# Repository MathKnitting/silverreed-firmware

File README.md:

# [Silverreed Firmware](./README.md)

<!-- Table of Contents -->

- [Installation](#installation)
- [Usage](#usage)
- [License](#license)

## Installation

This project leverages:
- PlatformIO for Arduino project management
- uv for Python dependency management
- taskipy for task automation

### Prerequisites

- Python 3.12 or higher
- [uv](https://docs.astral.sh/uv/) - Fast Python package installer

### Setup

1. Clone the repo
   ```shell
   git clone https://github.com/Knitall/silverreed-firmware.git
   cd silverreed-firmware
   ```

2. Install uv (if not already installed)
   ```shell
   curl -LsSf https://astral.sh/uv/install.sh | sh
   ```

3. Install dependencies
   ```shell
   uv sync --all-groups
   ```

4. Initialize the project
   ```shell
   uv run task init
   ```

## Usage

### Common Commands

```shell
# Build the firmware
uv run task build

# Build for specific environment
uv run task build -e uno
uv run task build -e unodebug    # With debug flags
uv run task build -e uno_r4_wifi # For Arduino UNO R4

# Upload to microcontroller
uv run task upload
uv run task upload -e uno

# Run tests
uv run task test
uv run task test -e simavr       # Run on AVR simulator
uv run task test -e native       # Run on native platform

# Run linter
uv run task lint

# Open serial monitor
uv run task monitor

# Documentation
uv run task docs-serve            # Serve locally with hot-reload
uv run task docs-build            # Build static site
uv run task docs-deploy           # Deploy to GitHub Pages

# Clean build artifacts
uv run task clean

# See all available tasks
uv run task --list
```

### Available Environments

- `uno` - Arduino UNO (default)
- `unodebug` - Arduino UNO with debug flags
- `uno_r4_wifi` - Arduino UNO R4 WiFi
- `simavr` - AVR simulator for testing
- `native` - Native platform for desktop tests

## License

Distributed under the MIT License. See [LICENSE](./LICENSE) for more information.

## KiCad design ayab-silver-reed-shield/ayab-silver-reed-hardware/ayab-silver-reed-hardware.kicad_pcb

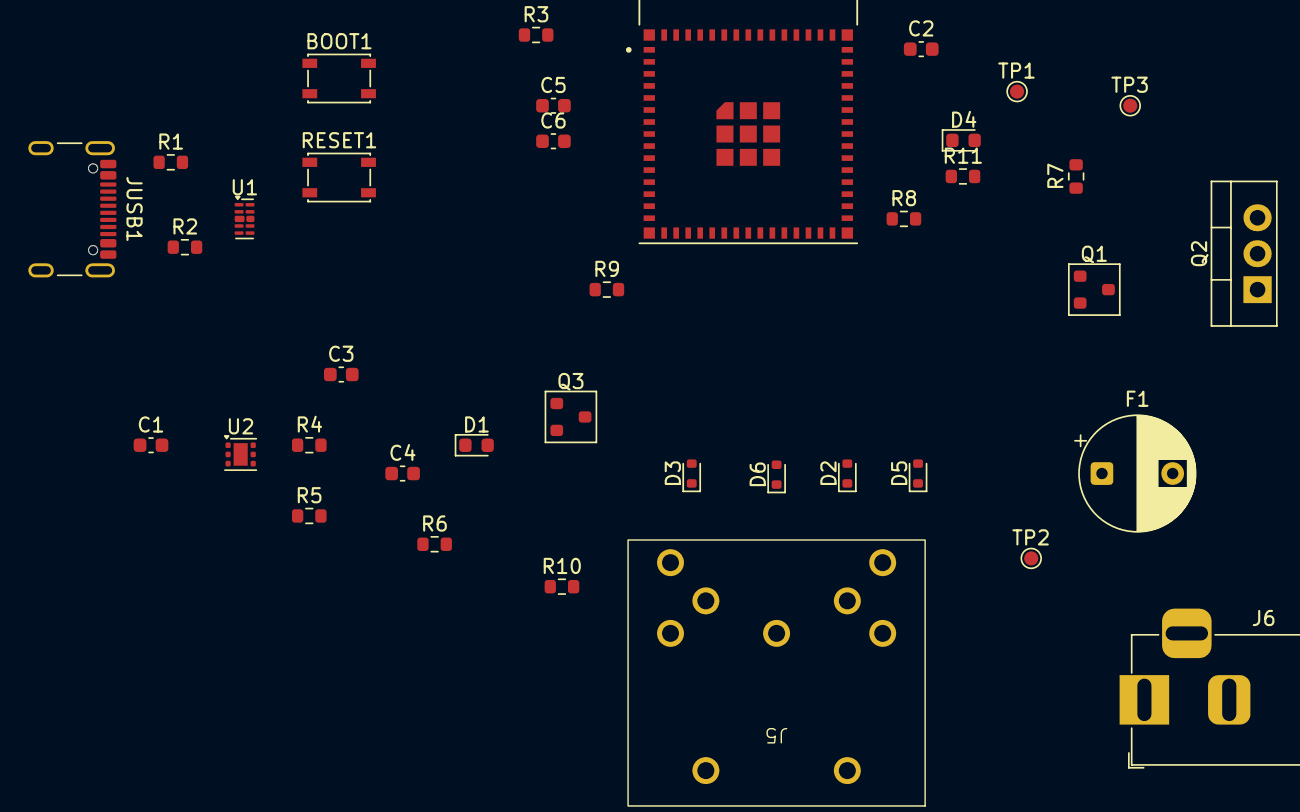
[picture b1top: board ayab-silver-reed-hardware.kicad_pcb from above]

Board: 2 copper layers, 38 parts (0 on the bottom side), 29 nets, no tracks yet.

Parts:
BOOT1: SW_SPST_PTS810
C1, C4, C6: 10uF; C_0603_1608Metric
C2, C3, C5: 0.1uF; C_0603_1608Metric
D1, D4: LED; LED_0603_1608Metric
D2, D3, D5, D6: 1N4148WT; D_SOD-523
F1: Polyfuse; CP_Radial_D8.0mm_P5.00mm
J5: DIN-7; DIN-704-M10
J6: Barrel_Jack; BarrelJack_Horizontal
JUSB1: USB_C_Receptacle_USB2.0_16P; USB_C_Receptacle_GCT_USB4105-xx-A_16P_TopMnt_Horizontal
Q1, Q3: MMBT2222A; SOT-23
Q2: Q_PMOS_GDS; TO-220-3_Vertical
R1, R2, R6: 5.1k; R_0603_1608Metric
R3, R4, R5, R7: 10k; R_0603_1608Metric
R8, R9, R10, R11: 1k; R_0603_1608Metric
RESET1: SW_SPST_PTS810
TP1: GND; TestPoint_Pad_D1.0mm
TP2: 16V; TestPoint_Pad_D1.0mm
TP3: 5V; TestPoint_Pad_D1.0mm
U1: D3V3XA4B10LP; Diodes_UDFN-10_1x2.5mm_P0.5mm
U2: TLV75801PDRV; WSON-6-1EP_2x2mm_P0.65mm_EP1x1.6mm
U3: ESP32-S3-MINI-1-N8; XCVR_ESP32-S3-MINI-1-N8

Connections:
/3V3: C4.2, C5.2, C6.2, R3.1, R4.1, R6.1, U2.1 (OUT), U3.3 (3V3)
/3vCCP: D2.2 (A), U3.19 (IO15)
/3vDOB: R9.2, U3.18 (IO14)
/3vHOK: D3.2 (A), U3.16 (IO12)
/3vKSL: D6.2 (A), U3.17 (IO13)
/3vND1: D5.2 (A), U3.20 (IO16)
/5VUSB: C1.2, J5.7, JUSB1.A4 (VBUS), JUSB1.A9 (VBUS), JUSB1.B4 (VBUS), JUSB1.B9 (VBUS), R10.1, TP3.1, U1.4, U2.4 (EN), U2.6 (IN)
/16VControlled: F1.1, J5.6, TP2.1
/16vIN: J6.1, Q2.3 (S), R7.2, R11.2
/CCP: D2.1 (K), J5.4
/DOB: J5.3, Q3.3 (C), R10.2
/ESP32_EN: C2.2, R3.2, U3.45 (EN)
/GPIO0: C3.2, U3.4 (IO0)
/HOK: D3.1 (K), J5.5
/KSL: D6.1 (K), J5.2
/ND1: D5.1 (K), J5.1
/SolenoidControl: R8.2, U3.21 (IO17)
/USB_N: JUSB1.A7 (D-), JUSB1.B7 (D-), U1.2, U3.23 (IO19)
/USB_P: JUSB1.A6 (D+), JUSB1.B6 (D+), U1.1, U3.24 (IO20)
GND: BOOT1.1, BOOT1.2, C1.1, C2.1, C3.1, C4.1, C5.1, C6.1, D1.1 (K), D4.1 (K), J5.8 (GND), J6.2, JUSB1.A1 (GND), JUSB1.A12 (GND), JUSB1.B1 (GND), JUSB1.B12 (GND), JUSB1.S1 (SHIELD), Q1.1 (E), Q3.1 (E), R1.2, R2.1, R5.2, RESET1.1, RESET1.2, TP1.1, U1.3 (VSS), U1.8 (VSS), U2.3 (GND), U2.7 (GND), U3.1 (GND), U3.2 (GND), U3.42 (GND), U3.43 (GND), U3.46 (GND), U3.47 (GND), U3.48 (GND), U3.49 (GND), U3.50 (GND), U3.51 (GND), U3.52 (GND), U3.53 (GND), U3.54 (GND), U3.55 (GND), U3.56 (GND), U3.57 (GND), U3.58 (GND), U3.59 (GND), U3.60 (GND), U3.61 (GND), U3.61_1 (GND), U3.61_2 (GND), U3.61_3 (GND), U3.61_4 (GND), U3.61_5 (GND), U3.61_6 (GND), U3.61_7 (GND), U3.61_8 (GND), U3.62 (GND), U3.63 (GND), U3.64 (GND), U3.65 (GND)
unnamed: D1.2 (A), R6.2
unnamed: D4.2 (A), R11.1
unnamed: JUSB1.A5 (CC1), R1.1
unnamed: JUSB1.B5 (CC2), R2.2
unnamed: Q1.2 (B), R8.1
unnamed: Q1.3 (C), Q2.1 (G), R7.1
unnamed: F1.2, Q2.2 (D)
unnamed: Q3.2 (B), R9.1
unnamed: R4.2, R5.1, U2.2 (FB)

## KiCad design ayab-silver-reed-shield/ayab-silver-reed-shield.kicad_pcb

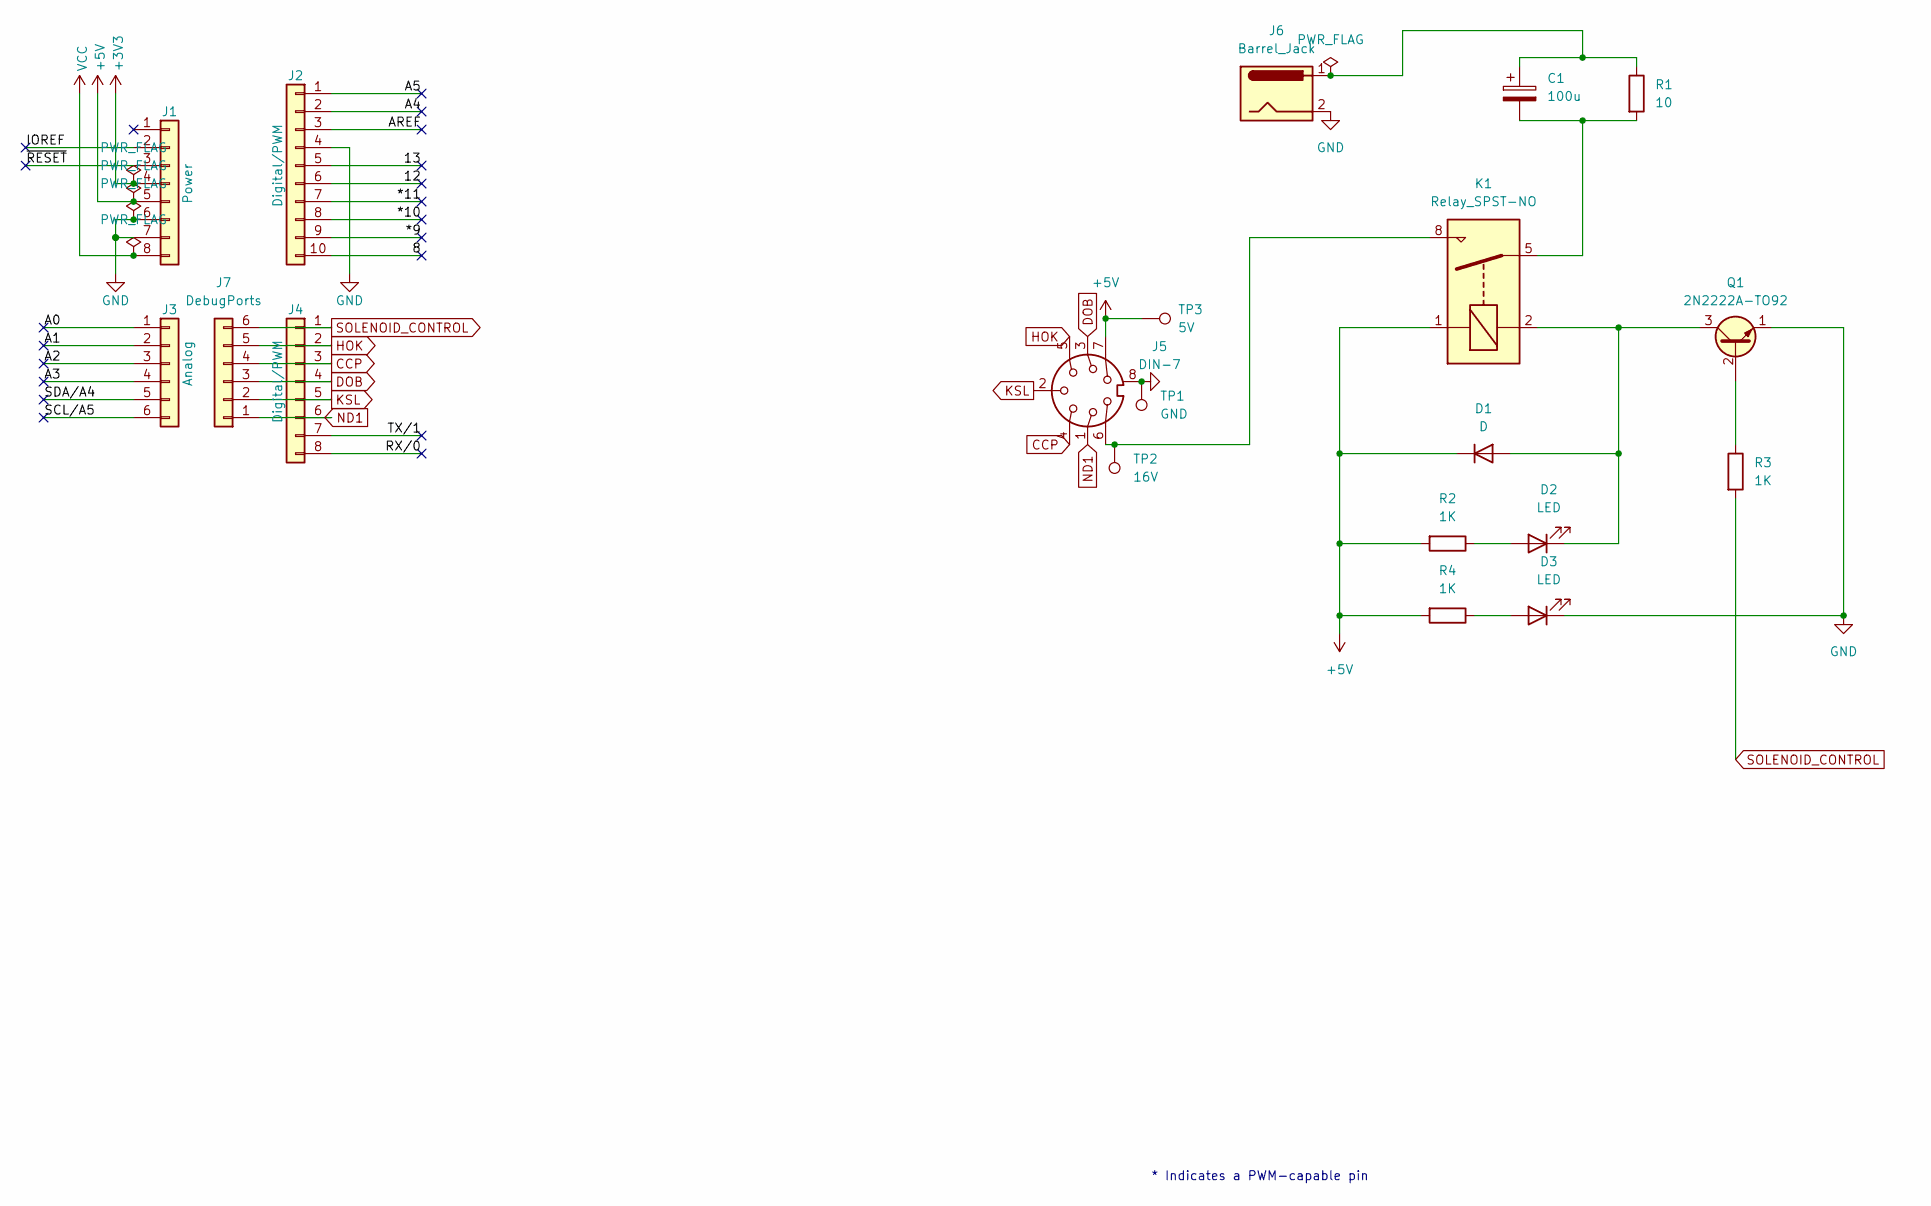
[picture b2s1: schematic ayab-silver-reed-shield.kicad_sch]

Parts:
C1: 100u; CP_6.3x11mm_horiz-R
D1: D; D_DO-41_SOD81_P7.62mm_Horizontal
D2, D3: LED; LED_D5.0mm
J1: Power; PinHeader_1x08_P2.54mm_Vertical
J2: Digital/PWM; PinHeader_1x10_P2.54mm_Vertical
J3: Analog; PinHeader_1x06_P2.54mm_Vertical
J4: Digital/PWM; PinHeader_1x08_P2.54mm_Vertical
J5: DIN-7; DIN-704-M10
J6: Barrel_Jack; BarrelJack_Horizontal
J7: DebugPorts; PinHeader_1x06_P2.54mm_Vertical
K1: Relay_SPST-NO; RELAY_G6DN-1A_OMR
Q1: 2N2222A-TO92; TO-92_Inline
R1: 10; R_Axial_Power_L20.0mm_W6.4mm_P25.40mm
R2, R3, R4: 1K; R_Axial_DIN0207_L6.3mm_D2.5mm_P2.54mm_Vertical
TP1: GND; TestPoint_Pad_D1.0mm
TP2: 16V; TestPoint_Pad_D1.0mm
TP3: 5V; TestPoint_Pad_D1.0mm

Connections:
+3V3: J1.4
+5V: D1.1 (K), J1.5, J5.7, K1.1, R2.2, R4.2, TP3.1
/8: J2.10
/12: J2.6
/13: J2.5
/*9: J2.9
/*10: J2.8
/*11: J2.7
/A0: J3.1
/A1: J3.2
/A2: J3.3
/A3: J3.4
/A4: J2.2
/A5: J2.1
/AREF: J2.3
/IOREF: J1.2
/RX/0: J4.8
/SCL/A5: J3.6
/SDA/A4: J3.5
/TX/1: J4.7
/~RESET: J1.3
CCP: J4.3, J5.4, J7.4
DOB: J4.4, J5.3, J7.3
GND: D3.1 (K), J1.6, J1.7, J2.4, J5.8 (GND), J6.2, Q1.1 (E), TP1.1
HOK: J4.2, J5.5, J7.5
KSL: J4.5, J5.2, J7.2
unnamed: C1.1, J6.1, R1.1
unnamed: C1.2, K1.5, R1.2
unnamed: D1.2 (A), D2.1 (K), K1.2, Q1.3 (C)
unnamed: D2.2 (A), R2.1
unnamed: D3.2 (A), R4.1
unnamed: J5.6, K1.8, TP2.1
unnamed: Q1.2 (B), R3.1
SOLENOID_CONTROL: J4.1, J7.6, R3.2
VCC: J1.8

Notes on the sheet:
* Indicates a PWM-capable pin

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
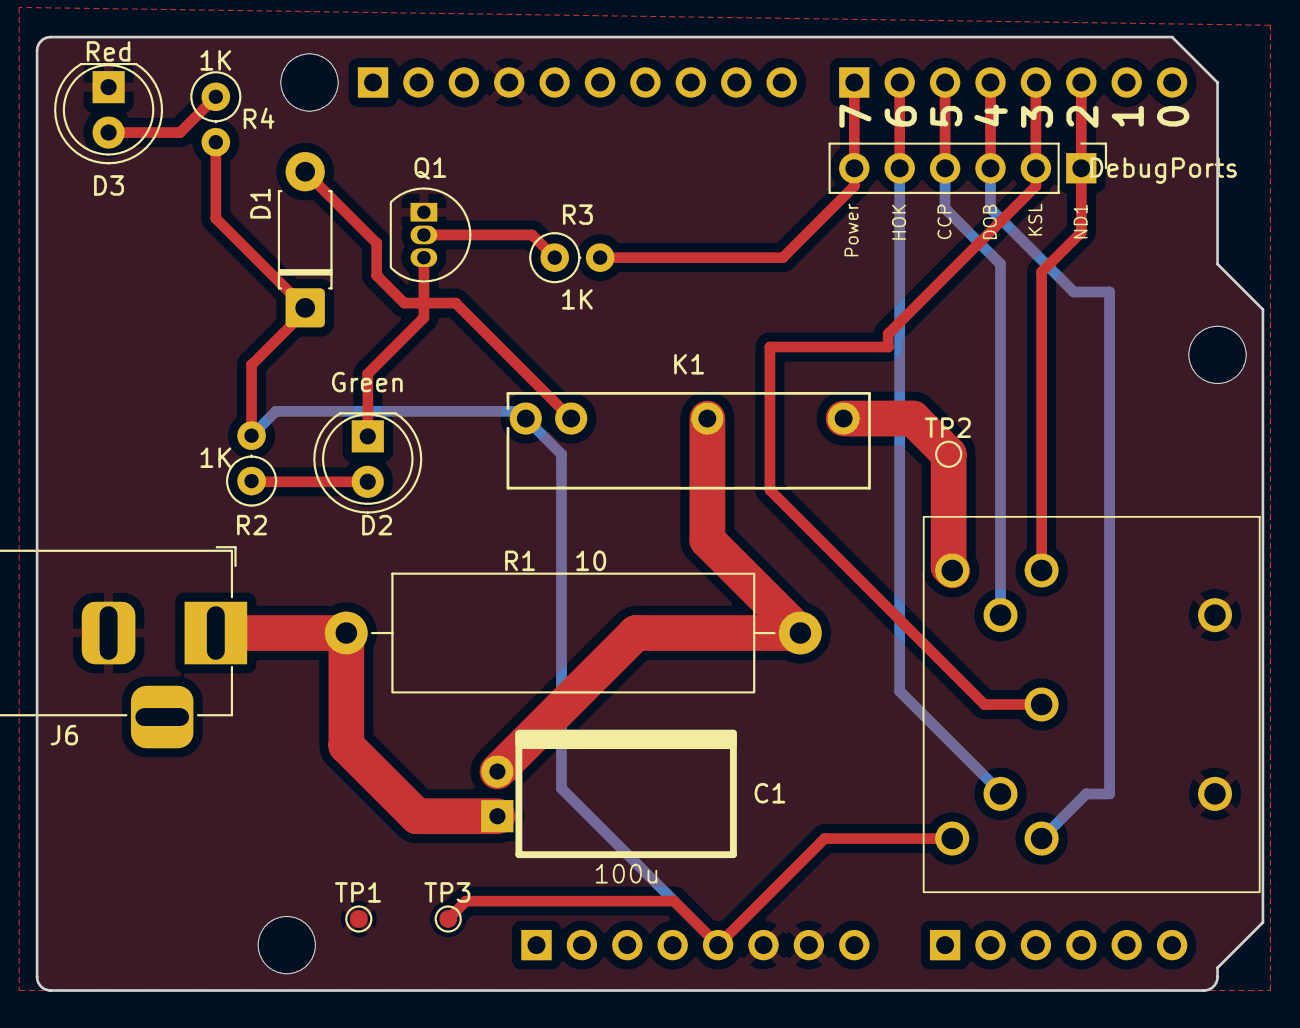
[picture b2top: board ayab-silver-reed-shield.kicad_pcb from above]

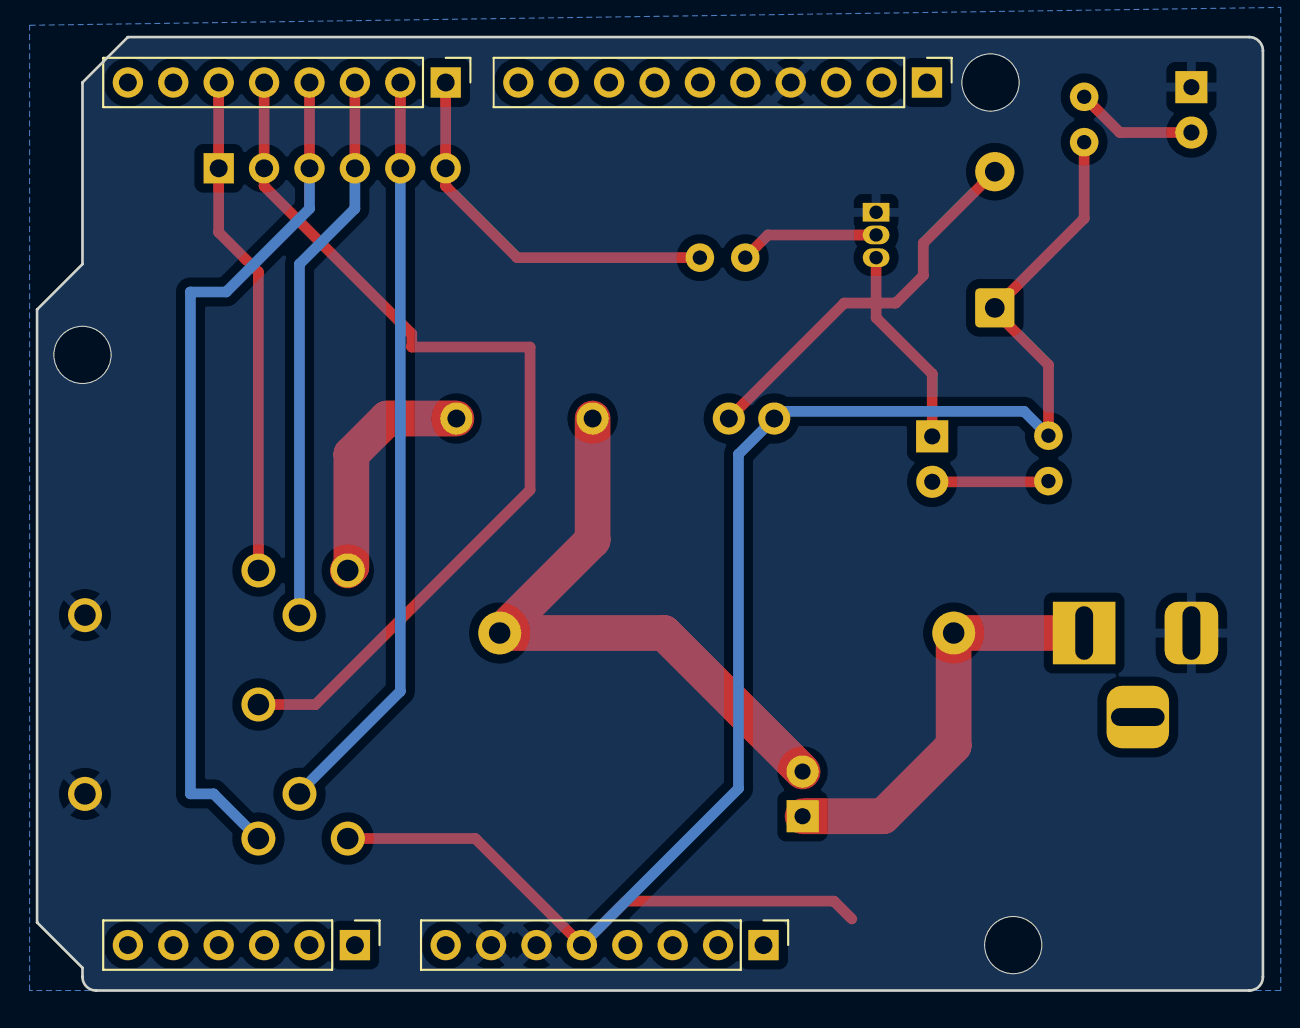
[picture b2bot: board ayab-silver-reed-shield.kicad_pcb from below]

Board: 2 copper layers, 68.6 x 53.3 mm, 23 parts (4 on the bottom side), 15 nets.

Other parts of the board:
MH1, MH2, MH3: MountingHole_3.2mm

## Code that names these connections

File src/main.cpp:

/**
 * Entry point of the Arduino.
 */
#include <Arduino.h>

#include "communication/ayab.h"
#include "config.h"
#include "debug.h"
#include "knitting.h"
#include "machine/carriage.h"

void setup() {
  /**
   * Setup run at the start of the Arduino.
   */
  // Set the pin modes for input pins.
  pinMode(PinsCorrespondance::ND1, INPUT_PULLUP);  // not used for now
  pinMode(PinsCorrespondance::KSL, INPUT_PULLUP);
  pinMode(PinsCorrespondance::DOB, OUTPUT);
  pinMode(PinsCorrespondance::CCP, INPUT_PULLUP);
  pinMode(PinsCorrespondance::HOK, INPUT_PULLUP);
  pinMode(PinsCorrespondance::SOLENOID_POWER, OUTPUT);

  // Initialize carriage output pins (DOB and SOLENOID_POWER) to safe state.
  // This handles DOB signal inversion automatically for platforms that need it.
  Carriage::secure_carriage();

  // Initialize the program singletons.
  Ayab.init();
  KnittingProcess.reset();

  // DEBUG
  DEBUG_START();
  DEBUG_PRINTLN("Init done");
}

void loop() {
  /**
   * Loop run continuously after the setup.
   */
  Ayab.update();
  KnittingProcess.knitting_loop();
}

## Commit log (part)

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2025-03-11 feat: initial commit
    First working version of the firmware with Ayab integration
2025-03-11 chore: add Dependabot configuration
2025-03-11 chore(deps): bump platformio from 6.1.16 to 6.1.17 (#9)
    * chore(deps): bump platformio from 6.1.16 to 6.1.17
    Bumps [platformio](https://github.com/platformio/platformio) from 6.1.16 to 6.1.17.
    - [Release notes](https://github.com/platformio/platformio/releases)
    - [Changelog](https://github.com/platformio/platformio-core/blob/develop/HISTORY.rst)
    - [Commits](https://github.com/platformio/platformio/compare/v6.1.16...v6.1.17)
    ---
2025-03-11 chore: add semantic release configuration
2025-03-11 Notes added by 'git notes add'
2025-03-11 chore(ci): rename job to CI
2025-03-11 chore(deps-dev): bump pre-commit from 2.21.0 to 4.1.0
    Bumps [pre-commit](https://github.com/pre-commit/pre-commit) from 2.21.0 to 4.1.0.
    - [Release notes](https://github.com/pre-commit/pre-commit/releases)
    - [Changelog](https://github.com/pre-commit/pre-commit/blob/main/CHANGELOG.md)
    - [Commits](https://github.com/pre-commit/pre-commit/compare/v2.21.0...v4.1.0)
    ---
    updated-dependencies:
2025-03-15 feat: add solenoid powering
2025-03-26 chore(deps-dev): bump pre-commit from 4.1.0 to 4.2.0 (#14)
    Bumps [pre-commit](https://github.com/pre-commit/pre-commit) from 4.1.0 to 4.2.0.
    - [Release notes](https://github.com/pre-commit/pre-commit/releases)
    - [Changelog](https://github.com/pre-commit/pre-commit/blob/main/CHANGELOG.md)
    - [Commits](https://github.com/pre-commit/pre-commit/compare/v4.1.0...v4.2.0)
    ---
    updated-dependencies:
2025-03-27 feat: add solenoid powering (#16)
2025-04-24 chore(deps): bump h11 from 0.14.0 to 0.16.0 in the pip group
    Bumps the pip group with 1 update: [h11](https://github.com/python-hyper/h11).
    Updates `h11` from 0.14.0 to 0.16.0
    - [Commits](https://github.com/python-hyper/h11/compare/v0.14.0...v0.16.0)
    ---
    updated-dependencies:
    - dependency-name: h11
2025-06-09 chore(deps-dev): bump pytest from 8.3.5 to 8.4.0
    Bumps [pytest](https://github.com/pytest-dev/pytest) from 8.3.5 to 8.4.0.
    - [Release notes](https://github.com/pytest-dev/pytest/releases)
    - [Changelog](https://github.com/pytest-dev/pytest/blob/main/CHANGELOG.rst)
    - [Commits](https://github.com/pytest-dev/pytest/compare/8.3.5...8.4.0)
    ---
    updated-dependencies:
2025-08-11 chore(deps-dev): bump pre-commit from 4.2.0 to 4.3.0
    Bumps [pre-commit](https://github.com/pre-commit/pre-commit) from 4.2.0 to 4.3.0.
    - [Release notes](https://github.com/pre-commit/pre-commit/releases)
    - [Changelog](https://github.com/pre-commit/pre-commit/blob/main/CHANGELOG.md)
    - [Commits](https://github.com/pre-commit/pre-commit/compare/v4.2.0...v4.3.0)
    ---
    updated-dependencies:
2025-09-14 Update hardware files
2025-11-10 chore(deps-dev): bump pytest from 8.3.5 to 9.0.0
    Bumps [pytest](https://github.com/pytest-dev/pytest) from 8.3.5 to 9.0.0.
    - [Release notes](https://github.com/pytest-dev/pytest/releases)
    - [Changelog](https://github.com/pytest-dev/pytest/blob/main/CHANGELOG.rst)
    - [Commits](https://github.com/pytest-dev/pytest/compare/8.3.5...9.0.0)
    ---
    updated-dependencies:
2025-11-23 Add PCB board design
2025-11-23 Add mass plan without gnd links
2025-11-23 Add text
2025-11-24 chore(deps-dev): bump pre-commit from 4.2.0 to 4.5.0
    Bumps [pre-commit](https://github.com/pre-commit/pre-commit) from 4.2.0 to 4.5.0.
    - [Release notes](https://github.com/pre-commit/pre-commit/releases)
    - [Changelog](https://github.com/pre-commit/pre-commit/blob/main/CHANGELOG.md)
    - [Commits](https://github.com/pre-commit/pre-commit/compare/v4.2.0...v4.5.0)
    ---
    updated-dependencies:
2025-12-07 fix: fix pin correspondances
2025-12-07 chore: exclude shield in pre commit
2025-12-07 chore(deps-dev): bump pre-commit from 4.2.0 to 4.5.0 (#26)
    Bumps [pre-commit](https://github.com/pre-commit/pre-commit) from 4.2.0 to 4.5.0.
    - [Release notes](https://github.com/pre-commit/pre-commit/releases)
    - [Changelog](https://github.com/pre-commit/pre-commit/blob/main/CHANGELOG.md)
    - [Commits](https://github.com/pre-commit/pre-commit/compare/v4.2.0...v4.5.0)
    ---
    updated-dependencies:
2025-12-07 fix: invert din pins
2025-12-07 chore(release): 1.1.1 [skip ci]
    ## [1.1.1](https://github.com/MathKnitting/silverreed-firmware/compare/v1.1.0...v1.1.1) (2025-12-07)
    ### Bug Fixes
    * invert din pins ([#27](https://github.com/MathKnitting/silverreed-firmware/issues/27)) ([6695316](https://github.com/MathKnitting/silverreed-firmware/commit/669531643c14b87d1e669180c153ba5a85fb1aad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
2025-12-07 chore(release): 1.2.0 [skip ci]
    # [1.2.0](https://github.com/MathKnitting/silverreed-firmware/compare/v1.1.1...v1.2.0) (2025-12-07)
    ### Features
    * add locals symbols ([f30d054](https://github.com/MathKnitting/silverreed-firmware/commit/f30d054b44b87ae6aae146c93429d9d44cc44d8c))
2025-12-08 chore(deps-dev): bump pytest from 8.3.5 to 9.0.2
    Bumps [pytest](https://github.com/pytest-dev/pytest) from 8.3.5 to 9.0.2.
    - [Release notes](https://github.com/pytest-dev/pytest/releases)
    - [Changelog](https://github.com/pytest-dev/pytest/blob/main/CHANGELOG.rst)
    - [Commits](https://github.com/pytest-dev/pytest/compare/8.3.5...9.0.2)
    ---
    updated-dependencies:
2025-12-19 feat: new board version with debug
2025-12-31 chore(deps-dev): bump pytest from 8.3.5 to 9.0.2 (#28)
    Bumps [pytest](https://github.com/pytest-dev/pytest) from 8.3.5 to 9.0.2.
    - [Release notes](https://github.com/pytest-dev/pytest/releases)
    - [Changelog](https://github.com/pytest-dev/pytest/blob/main/CHANGELOG.rst)
    - [Commits](https://github.com/pytest-dev/pytest/compare/8.3.5...9.0.2)
    ---
    updated-dependencies:
2025-12-31 chore(deps-dev): bump pre-commit from 4.5.0 to 4.5.1
    Bumps [pre-commit](https://github.com/pre-commit/pre-commit) from 4.5.0 to 4.5.1.
    - [Release notes](https://github.com/pre-commit/pre-commit/releases)
    - [Changelog](https://github.com/pre-commit/pre-commit/blob/main/CHANGELOG.md)
    - [Commits](https://github.com/pre-commit/pre-commit/compare/v4.5.0...v4.5.1)
    ---
    updated-dependencies:
2025-12-31 chore(release): 1.2.0 [skip ci]
    # [1.2.0](https://github.com/MathKnitting/silverreed-firmware/compare/v1.1.1...v1.2.0) (2025-12-31)
    ### Bug Fixes
    * finalize first working version ([#30](https://github.com/MathKnitting/silverreed-firmware/issues/30)) ([c7ad95c](https://github.com/MathKnitting/silverreed-firmware/commit/c7ad95c4314d1c6c2ee076427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
    ### Features
    * add locals symbols ([fd517f3](https://github.com/MathKnitting/silverreed-firmware/commit/fd517f3c698f4c5722ead6b4d4d3c90bd071c17b))
2025-12-31 chore: some refactors
2025-12-31 chore(release): 1.2.0 [skip ci]
    # [1.2.0](https://github.com/MathKnitting/silverreed-firmware/compare/v1.1.1...v1.2.0) (2025-12-31)
    ### Bug Fixes
    * finalize first working version ([#30](https://github.com/MathKnitting/silverreed-firmware/issues/30)) ([c7ad95c](https://github.com/MathKnitting/silverreed-firmware/commit/c7ad95c4314d1c6c2ee076427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
    ### Features
    * add locals symbols ([fd517f3](https://github.com/MathKnitting/silverreed-firmware/commit/fd517f3c698f4c5722ead6b4d4d3c90bd071c17b))
    * add solenoid power handling ([3b7e48b](https://github.com/MathKnitting/silverreed-firmware/commit/3b7e48b46baa6f32d730e03ace42ea97c33ac6ea))
2026-01-01 chore(release): 1.2.0 [skip ci]
    # [1.2.0](https://github.com/MathKnitting/silverreed-firmware/compare/v1.1.1...v1.2.0) (2026-01-01)
    ### Bug Fixes
    * finalize first working version ([#30](https://github.com/MathKnitting/silverreed-firmware/issues/30)) ([c7ad95c](https://github.com/MathKnitting/silverreed-firmware/commit/c7ad95c4314d1c6c2ee076427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
    ### Features
    * add locals symbols ([fd517f3](https://github.com/MathKnitting/silverreed-firmware/commit/fd517f3c698f4c5722ead6b4d4d3c90bd071c17b))
    * add solenoid power handling ([3b7e48b](https://github.com/MathKnitting/silverreed-firmware/commit/3b7e48b46baa6f32d730e03ace42ea97c33ac6ea))
2026-01-01 chore(release): 1.2.0 [skip ci]
    # [1.2.0](https://github.com/MathKnitting/silverreed-firmware/compare/v1.1.1...v1.2.0) (2026-01-01)
    ### Bug Fixes
    * finalize first working version ([#30](https://github.com/MathKnitting/silverreed-firmware/issues/30)) ([c7ad95c](https://github.com/MathKnitting/silverreed-firmware/commit/c7ad95c4314d1c6c2ee076427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
    * lint ([c80a39c](https://github.com/MathKnitting/silverreed-firmware/commit/c80a39c5ddb5875db649f7e520944371f325c9f3))
    ### Features
    * add locals symbols ([fd517f3](https://github.com/MathKnitting/silverreed-firmware/commit/fd517f3c698f4c5722ead6b4d4d3c90bd071c17b))
2026-01-01 chore(release): 1.2.1 [skip ci]
    ## [1.2.1](https://github.com/MathKnitting/silverreed-firmware/compare/v1.2.0...v1.2.1) (2026-01-01)
    ### Bug Fixes
    * semantic release ([b06037a](https://github.com/MathKnitting/silverreed-firmware/commit/b06037a9ea68be5e7711d63043af6e667b54706c))
2026-01-01 chore(release): 1.2.3
    ## [1.2.3](https://github.com/MathKnitting/silverreed-firmware/compare/v1.2.2...v1.2.3) (2026-01-01)
    ### Bug Fixes
    * semantic release ([6e4f430](https://github.com/MathKnitting/silverreed-firmware/commit/6e4f430dffe6e37d0e6e399d1a9fcd2ed4efa776))
2026-01-01 chore: avoid running semantic release if not required
2026-01-01 feat: add firmware to release
2026-01-01 fix: r4 firmware
2026-01-01 fix: release artifacts
2026-01-01 feat: add firmware version handling
2026-01-02 chore: add references
2026-01-18 chore(release): 1.4.1
    ## [1.4.1](https://github.com/MathKnitting/silverreed-firmware/compare/v1.4.0...v1.4.1) (2026-01-18)
    ### Bug Fixes
    * needle start of needle synchronization with start and end of pattern [#34](https://github.com/MathKnitting/silverreed-firmware/issues/34) ([7ec3f5b](https://github.com/MathKnitting/silverreed-firmw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
2026-01-18 fix: force solenoid poweroff when resetting carriage #36
2026-01-18 fix: stop knitting directly when a last line received #39
2026-01-18 chore(deps): update deps
2026-01-21 fix: allow knitting cancelation and restarting
2026-01-22 deploy: 7d15a53dcc555ec0853898e9672491a0d3420ed0
2026-01-27 chore(deps-dev): bump mkdocstrings from 1.0.0 to 1.0.2
    Bumps [mkdocstrings](https://github.com/mkdocstrings/mkdocstrings) from 1.0.0 to 1.0.2.
    - [Release notes](https://github.com/mkdocstrings/mkdocstrings/releases)
    - [Changelog](https://github.com/mkdocstrings/mkdocstrings/blob/main/CHANGELOG.md)
    - [Commits](https://github.com/mkdocstrings/mkdocstrings/compare/1.0.0...1.0.2)
    ---
    updated-dependencies:
2026-02-10 chore(deps): bump platformio from 6.1.18 to 6.1.19
    Bumps [platformio](https://github.com/platformio/platformio) from 6.1.18 to 6.1.19.
    - [Release notes](https://github.com/platformio/platformio/releases)
    - [Changelog](https://github.com/platformio/platformio-core/blob/develop/HISTORY.rst)
    - [Commits](https://github.com/platformio/platformio/compare/v6.1.18...v6.1.19)
    ---
    updated-dependencies:
2026-02-17 chore(deps-dev): bump pymdown-extensions from 10.20 to 10.21
    Bumps [pymdown-extensions](https://github.com/facelessuser/pymdown-extensions) from 10.20 to 10.21.
    - [Release notes](https://github.com/facelessuser/pymdown-extensions/releases)
    - [Commits](https://github.com/facelessuser/pymdown-extensions/compare/10.20...10.21)
    ---
    updated-dependencies:
    - dependency-name: pymdown-extensions
2026-03-10 chore(deps-dev): bump mkdocs-material from 9.7.1 to 9.7.5
    Bumps [mkdocs-material](https://github.com/squidfunk/mkdocs-material) from 9.7.1 to 9.7.5.
    - [Release notes](https://github.com/squidfunk/mkdocs-material/releases)
    - [Changelog](https://github.com/squidfunk/mkdocs-material/blob/master/CHANGELOG)
    - [Commits](https://github.com/squidfunk/mkdocs-material/compare/9.7.1...9.7.5)
    ---
    updated-dependencies:
2026-03-26 chore(deps): bump the uv group across 1 directory with 2 updates
    Bumps the uv group with 2 updates in the / directory: [requests](https://github.com/psf/requests) and [starlette](https://github.com/Kludex/starlette).
    Updates `requests` from 2.32.5 to 2.33.0
    - [Release notes](https://github.com/psf/requests/releases)
    - [Changelog](https://github.com/psf/requests/blob/main/HISTORY.md)
    - [Commits](https://github.com/psf/requests/compare/v2.32.5...v2.33.0)
    Updates `starlette` from 0.46.2 to 0.49.1
2026-06-23 circular pcb fun
